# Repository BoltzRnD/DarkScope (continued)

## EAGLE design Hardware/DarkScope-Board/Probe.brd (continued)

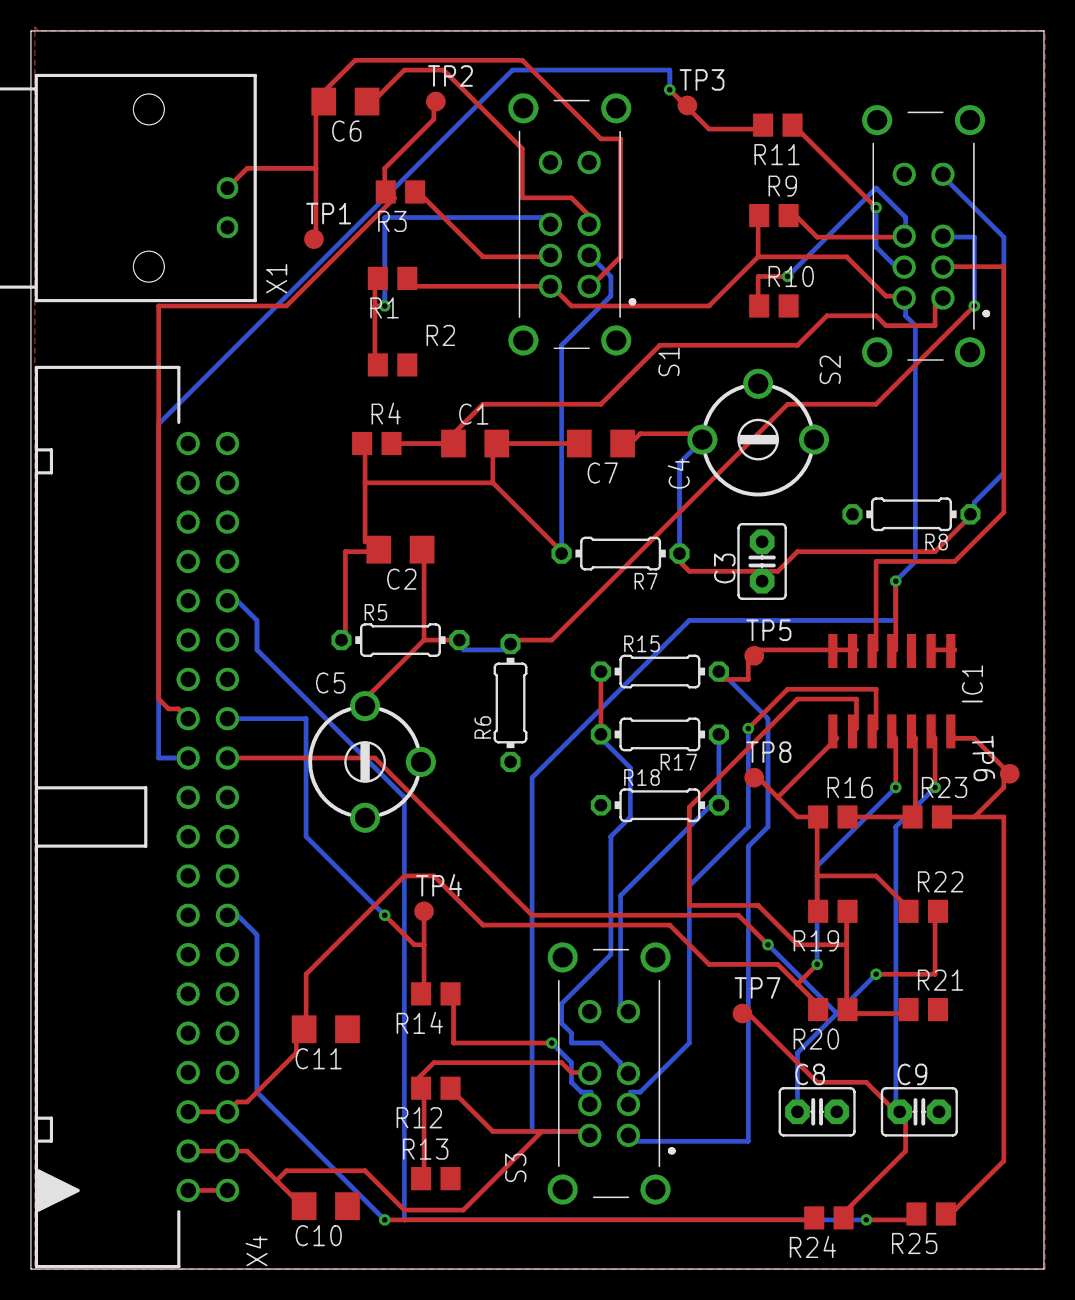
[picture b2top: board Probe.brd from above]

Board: 2 copper layers, 65.5 x 80.0 mm, 50 parts (0 on the bottom side), 33 nets.

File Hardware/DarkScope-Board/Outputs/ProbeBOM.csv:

"Part";"Value";"Device";"Package";"Description";"ARROW_PART_NUMBER";"ARROW_PRICE-STOCK";"DESCRIPTION";"HEIGHT";"MANUFACTURER_NAME";"MANUFACTURER_PART_NUMBER";"MF";"MOUSER_PART_NUMBER";"MOUSER_PRICE-STOCK";"MPN";"OC_FARNELL";"OC_NEWARK";"POPULARITY";"SPICEPREFIX";"TP_SIGNAL_NAME";
"C1";"220pF";"C-EUC1206";"C1206";"CAPACITOR, European symbol";"";"";"";"";"";"";"";"";"";"";"";"";"54";"C";"";
"C2";"3pF";"C-EUC1206";"C1206";"CAPACITOR, European symbol";"";"";"";"";"";"";"";"";"";"";"";"";"54";"C";"";
"C3";"120pF";"C2,5-3";"C2.5-3";"CAPACITOR";"";"";"";"";"";"";"";"";"";"";"";"";"38";"";"";
"C4";"30pF";"C-TRIMM808";"CTRIM808-BC";"Trimm capacitor";"";"";"";"";"";"";"";"";"";"";"";"";"3";"C";"";
"C5";"30pF";"C-TRIMM808";"CTRIM808-BC";"Trimm capacitor";"";"";"";"";"";"";"";"";"";"";"";"";"3";"C";"";
"C6";"0.1u";"C-EUC1206";"C1206";"CAPACITOR, European symbol";"";"";"";"";"";"";"";"";"";"";"";"";"54";"C";"";
"C7";"1pF";"C-EUC1206";"C1206";"CAPACITOR, European symbol";"";"";"";"";"";"";"";"";"";"";"";"";"54";"C";"";
"C8";"120pF";"C2,5-3";"C2.5-3";"CAPACITOR";"";"";"";"";"";"";"";"";"";"";"";"";"38";"";"";
"C9";"0.1u";"C2,5-3";"C2.5-3";"CAPACITOR";"";"";"";"";"";"";"";"";"";"";"";"";"38";"";"";
"C10";"0.1uF";"C-EUC1206";"C1206";"CAPACITOR, European symbol";"";"";"";"";"";"";"";"";"";"";"";"";"54";"C";"";
"C11";"0.1uF";"C-EUC1206";"C1206";"CAPACITOR, European symbol";"";"";"";"";"";"";"";"";"";"";"";"";"54";"C";"";
"IC1";"TL084D";"TL084D";"SO14";"OP AMP";"";"";"";"";"";"";"";"";"";"";"";"";"4";"X";"";
"R1";"10K";"R-US_R0805";"R0805";"RESISTOR, American symbol";"";"";"";"";"";"";"";"";"";"";"";"";"85";"R";"";
"R2";"3.3K";"R-US_R0805";"R0805";"RESISTOR, American symbol";"";"";"";"";"";"";"";"";"";"";"";"";"85";"R";"";
"R3";"1.5K";"R-US_R0805";"R0805";"RESISTOR, American symbol";"";"";"";"";"";"";"";"";"";"";"";"";"85";"R";"";
"R4";"100K";"R-US_R0805";"R0805";"RESISTOR, American symbol";"";"";"";"";"";"";"";"";"";"";"";"";"85";"R";"";
"R5";"1.8M 1%";"R-EU_0204/7";"0204/7";"RESISTOR, European symbol";"";"";"";"";"";"";"";"";"";"";"";"";"79";"R";"";
"R6";"200K 1%";"R-EU_0204/7";"0204/7";"RESISTOR, European symbol";"";"";"";"";"";"";"";"";"";"";"";"";"79";"R";"";
"R7";"2M 1%";"R-EU_0204/7";"0204/7";"RESISTOR, European symbol";"";"";"";"";"";"";"";"";"";"";"";"";"79";"R";"";
"R8";"20K 1%";"R-EU_0204/7";"0204/7";"RESISTOR, European symbol";"";"";"";"";"";"";"";"";"";"";"";"";"79";"R";"";
"R9";"10K";"R-US_R0805";"R0805";"RESISTOR, American symbol";"";"";"";"";"";"";"";"";"";"";"";"";"85";"R";"";
"R10";"3.3K";"R-US_R0805";"R0805";"RESISTOR, American symbol";"";"";"";"";"";"";"";"";"";"";"";"";"85";"R";"";
"R11";"1.5K";"R-US_R0805";"R0805";"RESISTOR, American symbol";"";"";"";"";"";"";"";"";"";"";"";"";"85";"R";"";
"R12";"10K";"R-US_R0805";"R0805";"RESISTOR, American symbol";"";"";"";"";"";"";"";"";"";"";"";"";"85";"R";"";
"R13";"3.3K";"R-US_R0805";"R0805";"RESISTOR, American symbol";"";"";"";"";"";"";"";"";"";"";"";"";"85";"R";"";
"R14";"1.5K";"R-US_R0805";"R0805";"RESISTOR, American symbol";"";"";"";"";"";"";"";"";"";"";"";"";"85";"R";"";
"R15";"300E";"R-EU_0204/7";"0204/7";"RESISTOR, European symbol";"";"";"";"";"";"";"";"";"";"";"";"";"79";"R";"";
"R16";"120e";"R-US_R0805";"R0805";"RESISTOR, American symbol";"";"";"";"";"";"";"";"";"";"";"";"";"85";"R";"";
"R17";"180E";"R-EU_0204/7";"0204/7";"RESISTOR, European symbol";"";"";"";"";"";"";"";"";"";"";"";"";"79";"R";"";
"R18";"120E";"R-EU_0204/7";"0204/7";"RESISTOR, European symbol";"";"";"";"";"";"";"";"";"";"";"";"";"79";"R";"";
"R19";"1K";"R-US_R0805";"R0805";"RESISTOR, American symbol";"";"";"";"";"";"";"";"";"";"";"";"";"85";"R";"";
"R20";"3K";"R-US_R0805";"R0805";"RESISTOR, American symbol";"";"";"";"";"";"";"";"";"";"";"";"";"85";"R";"";
"R21";"150E";"R-US_R0805";"R0805";"RESISTOR, American symbol";"";"";"";"";"";"";"";"";"";"";"";"";"85";"R";"";
"R22";"120E";"R-US_R0805";"R0805";"RESISTOR, American symbol";"";"";"";"";"";"";"";"";"";"";"";"";"85";"R";"";
"R23";"100k";"R-US_R0805";"R0805";"RESISTOR, American symbol";"";"";"";"";"";"";"";"";"";"";"";"";"85";"R";"";
"R24";"100K";"R-US_R0805";"R0805";"RESISTOR, American symbol";"";"";"";"";"";"";"";"";"";"";"";"";"85";"R";"";
"R25";"1k";"R-US_R0805";"R0805";"RESISTOR, American symbol";"";"";"";"";"";"";"";"";"";"";"";"";"85";"R";"";
"S1";"DC-AC-GND";"EG2301";"EG2301";"Slide Switches DP3T PC MNT SLIDE";"";"";"Slide Switches DP3T PC MNT SLIDE";"11mm";"E-Switch";"EG2301";"";"612-EG2301";"https://www.mouser.co.uk/ProductDetail/E-Switch/EG2301?qs=6C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";"";"";"";"";"";"";
"S2";"EG2301";"EG2301";"EG2301";"Slide Switches DP3T PC MNT SLIDE";"";"";"Slide Switches DP3T PC MNT SLIDE";"11mm";"E-Switch";"EG2301";"";"612-EG2301";"https://www.mouser.co.uk/ProductDetail/E-Switch/EG2301?qs=6C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";"";"";"";"";"";"";
"S3";"EG2301";"EG2301";"EG2301";"Slide Switches DP3T PC MNT SLIDE";"";"";"Slide Switches DP3T PC MNT SLIDE";"11mm";"E-Switch";"EG2301";"";"612-EG2301";"https://www.mouser.co.uk/ProductDetail/E-Switch/EG2301?qs=6C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";"";"";"";"";"";"";
"TP1";"TPB1,27";"TPB1,27";"B1,27";"Test pad";"";"";"";"";"";"";"";"";"";"";"";"";"19";"";"";
"TP2";"TPB1,27";"TPB1,27";"B1,27";"Test pad";"";"";"";"";"";"";"";"";"";"";"";"";"19";"";"";
"TP3";"TPB1,27";"TPB1,27";"B1,27";"Test pad";"";"";"";"";"";"";"";"";"";"";"";"";"19";"";"";
"TP4";"TPB1,27";"TPB1,27";"B1,27";"Test pad";"";"";"";"";"";"";"";"";"";"";"";"";"19";"";"";
"TP5";"TPB1,27";"TPB1,27";"B1,27";"Test pad";"";"";"";"";"";"";"";"";"";"";"";"";"19";"";"";
"TP6";"TPB1,27";"TPB1,27";"B1,27";"Test pad";"";"";"";"";"";"";"";"";"";"";"";"";"19";"";"";
"TP7";"TPB1,27";"TPB1,27";"B1,27";"Test pad";"";"";"";"";"";"";"";"";"";"";"";"";"19";"";"";
"TP8";"TPB1,27";"TPB1,27";"B1,27";"Test pad";"";"";"";"";"";"";"";"";"";"";"";"";"19";"";"";
"X1";"1-227161-0";"1-227161-0";"AMP_227161";"JACK,  RIGHT ANGLE, 50 OHM, PCB, BNC";"";"";"";"";"";"";"TYCO ELECTRONICS";"";"";"1-227161";"unknown";"33B3200";"0";"";"";
"X4";"2540-5";"2540-5";"PAK100/2500-5-40";"3M (TM) Pak 100 4-Wall Header";"";"";"";"";"";"";"";"";"";"";"9838414";"unknown";"0";"";"";

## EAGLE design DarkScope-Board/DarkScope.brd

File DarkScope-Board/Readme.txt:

This Folder will be Updated with Schematics and Board Files For the Darkscope.

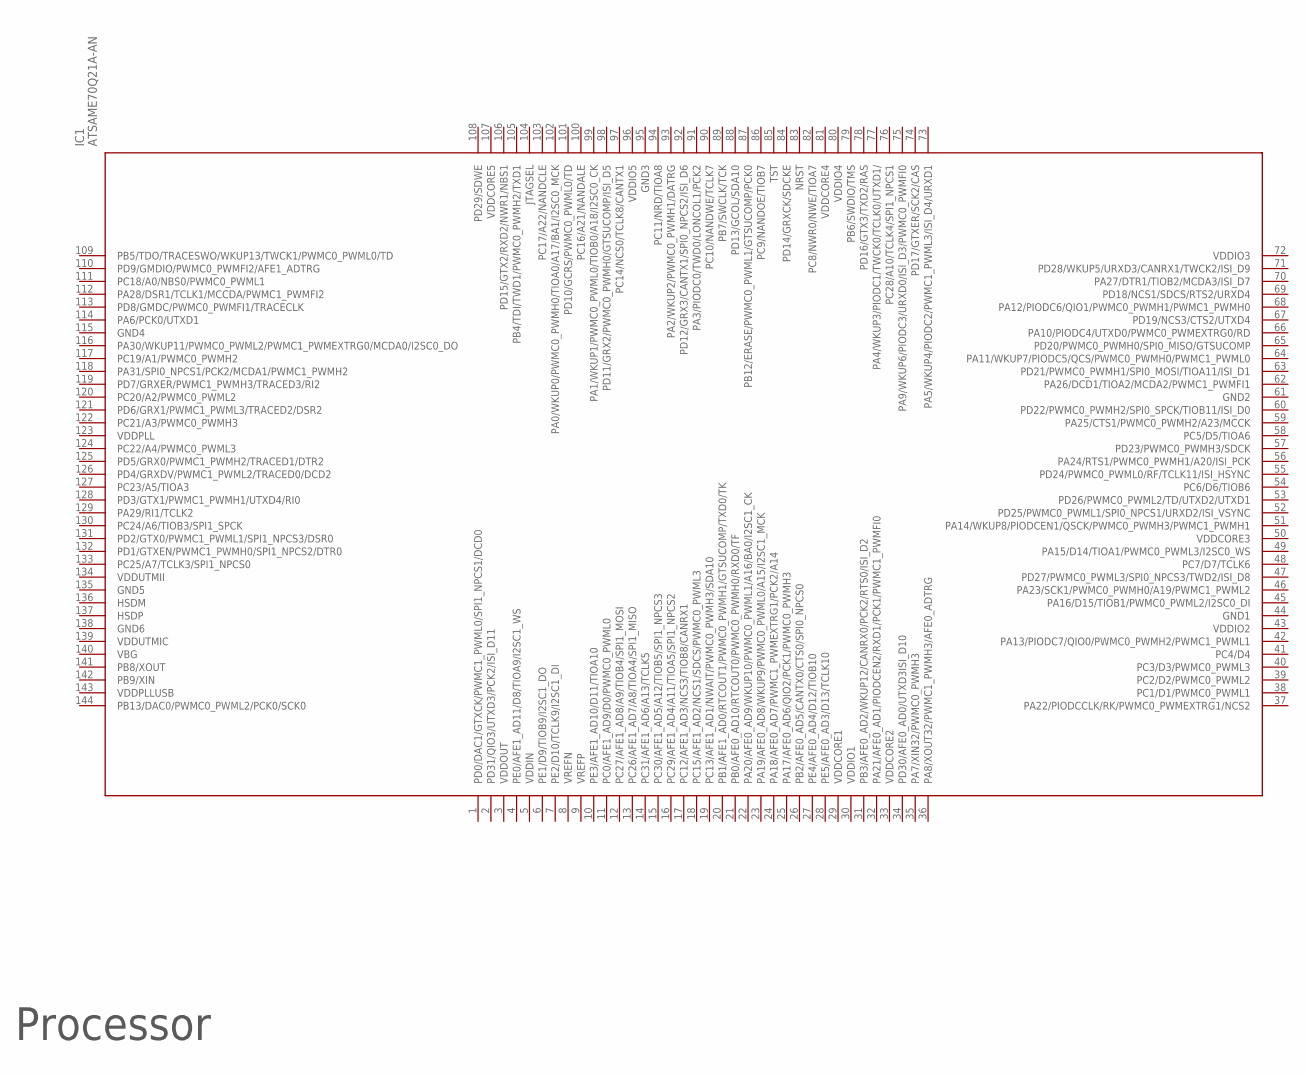
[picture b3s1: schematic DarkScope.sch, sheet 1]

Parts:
IC1: ATSAME70Q21A-AN; QFP50P2200X2200X160-144N

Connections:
GND1: IC1.44 (GND1)
GND2: IC1.61 (GND2)
GND3: IC1.95 (GND3)
GND4: IC1.115 (GND4)
GND5: IC1.135 (GND5)
GND6: IC1.138 (GND6)
VDDCORE1: IC1.29 (VDDCORE1)
VDDCORE2: IC1.33 (VDDCORE2)
VDDCORE3: IC1.50 (VDDCORE3)
VDDCORE4: IC1.81 (VDDCORE4)
VDDCORE5: IC1.107 (VDDCORE5)
VDDIN: IC1.5 (VDDIN)
VDDIO1: IC1.30 (VDDIO1)
VDDIO2: IC1.43 (VDDIO2)
VDDIO3: IC1.72 (VDDIO3)
VDDIO4: IC1.80 (VDDIO4)
VDDIO5: IC1.96 (VDDIO5)
VDDOUT: IC1.3 (VDDOUT)
VDDPLL: IC1.123 (VDDPLL)
VDDPLLUSB: IC1.143 (VDDPLLUSB)
VDDUTMIC: IC1.139 (VDDUTMIC)
VDDUTMII: IC1.134 (VDDUTMII)

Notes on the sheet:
Processor

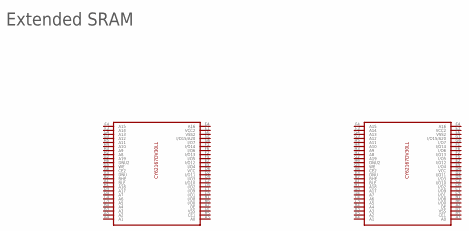
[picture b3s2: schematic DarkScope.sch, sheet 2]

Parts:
U$22, U$23: CY62167DV30LLCY62167DV30LL-55BVI; BGA48C75P6X8_950X800X100

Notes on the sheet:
Extended SRAM

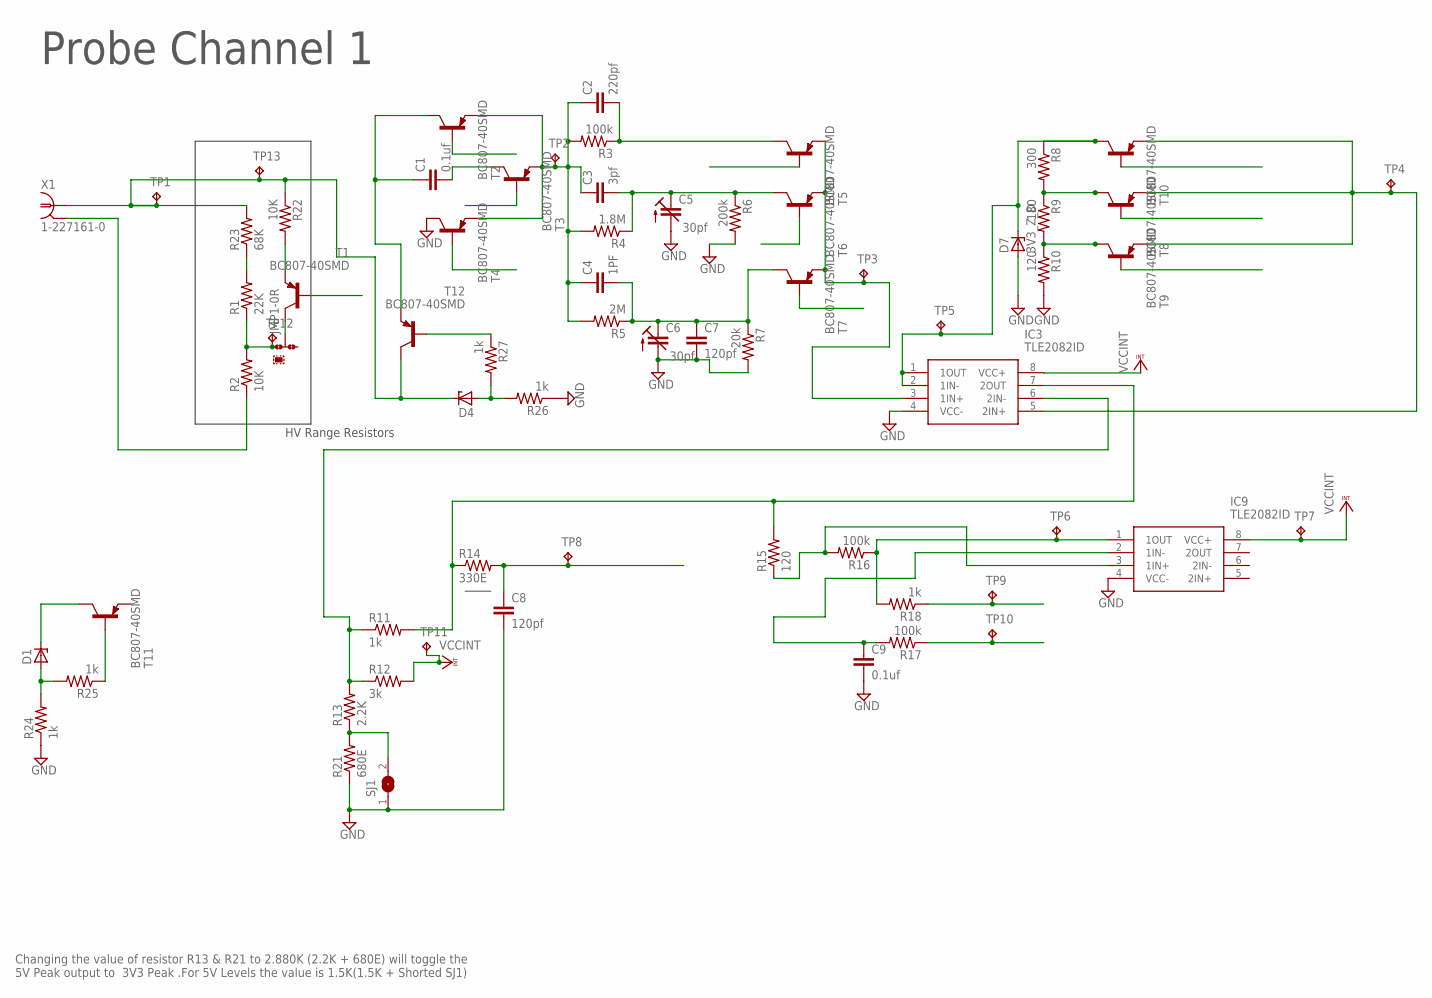
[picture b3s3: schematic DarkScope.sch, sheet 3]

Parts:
C1, C9: 0.1uf; C0603
C2: 220pf; C0603
C3: 3pf; C0603
C4: 1PF; C0603
C5, C6: 30pf; CTRIM3018_11
C7, C8: 120pf; C0603
D1, D4: ZENER-DIODESOD80C; SOD80C
D7: 3V3_Z_D; SOD80C
IC3, IC9: TLE2082ID; SOIC127P600X175-8N
JMP1: 0R-JUMPC; C0R-JMP
R1: 22K; R0603
R2, R22: 10K; R0603
R3, R16, R17: 100k; R0603
R4: 1.8M; R0603
R5: 2M; R0603
R6: 200k; R0603
R7: 20k; R0603
R8: 300; R0603
R9: 180; R0603
R10, R15: 120; R0603
R11, R18, R24, R25, R26, R27: 1k; R0603
R12: 3k; R0603
R13: 2.2K; R0603
R14: 330E; R0603
R21: 680E; R0603
R23: 68K; R0603
SJ1: SJ
T1, T2, T3, T4, T5, T6, T7, T8, T9, T10, T11, T12: BC807-40SMD; SOT23-BEC
TP1, TP2, TP3, TP4, TP5, TP6, TP7, TP8, TP9, TP10, TP11, TP12, TP13: TPTP07R; TP07R
X1: 1-227161-0; AMP_227161

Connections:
+5V/1: IC3.8 (VCC+), IC9.8 (VCC+), R12.2, TP7.TP, TP11.TP; also elsewhere on the board
GND: C5.- (A), C6.- (A), C7.2, C8.2, C9.2, D7.A, IC3.4 (VCC-), IC9.4 (VCC-), R6.2, R7.2, R10.2, R21.1, SJ1.1, T4.C; also elsewhere on the board
unnamed: R2.1, X1.2
unnamed: JMP1.1, R1.1, R2.2, TP12.TP
unnamed: C1.2, T3.C
unnamed: R8.2, R9.1, T8.C
unnamed: D4.C, R22.1, R23.2, T12.C, TP1.TP, TP13.TP, X1.1
unnamed: C2.1, C3.1, C4.1, R3.2, R4.2, R5.2, T2.E, T3.E, T4.E, TP2.TP
unnamed: C4.2, C6.+ (E), C7.1, R5.1, R7.1, T7.C
unnamed: C2.2, R3.1, T5.C
unnamed: C3.2, C5.+ (E), R4.1, R6.1, T6.C
unnamed: R9.2, R10.1, T9.C
unnamed: IC3.3 (1IN+), T5.E, T6.E, T7.E, TP3.TP
unnamed: IC3.5 (2IN+), T8.E, T9.E, T10.E, TP4.TP
unnamed: IC3.6 (2IN-), R11.1, R12.1, R13.2
unnamed: IC3.7 (2OUT), R11.2, R14.1, R15.2
unnamed: C8.1, R14.2, TP8.TP
unnamed: IC9.3 (1IN+), R15.1, R16.2
unnamed: IC9.1 (1OUT), R16.1, R18.2, TP6.TP
unnamed: C9.1, IC9.2 (1IN-), R17.2
unnamed: R17.1, TP10.TP
unnamed: R18.1, TP9.TP
unnamed: D7.C, IC3.1 (1OUT), IC3.2 (1IN-), R8.1, T10.C, TP5.TP
unnamed: R13.1, R21.2, SJ1.2
unnamed: R22.2, T1.E
unnamed: R1.2, R23.1
unnamed: JMP1.2, T1.C
unnamed: D1.A, R24.2, R25.2
unnamed: R25.1, T11.B
unnamed: D1.C, T11.C
unnamed: D4.A, R26.2, R27.2
unnamed: R27.1, T12.B
unnamed: C1.1, T2.C, T12.E

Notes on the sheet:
Probe Channel 1
HV Range Resistors
Changing the value of resistor R13 & R21 to 2.880K (2.2K + 680E) will toggle the 5V Peak output to 3V3 Peak .For 5V Levels the value is 1.5K(1.5K + Shorted SJ1)

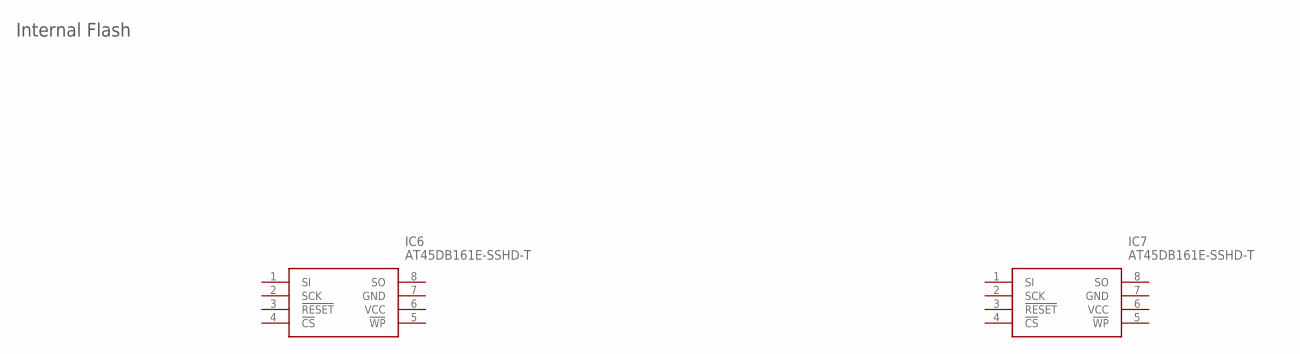
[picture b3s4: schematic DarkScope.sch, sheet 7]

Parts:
IC6, IC7: AT45DB161E-SSHD-T; SOIC127P600X175-8N

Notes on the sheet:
Internal Flash

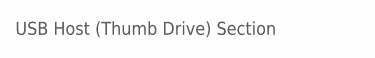
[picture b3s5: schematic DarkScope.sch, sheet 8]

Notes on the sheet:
USB Host (Thumb Drive) Section

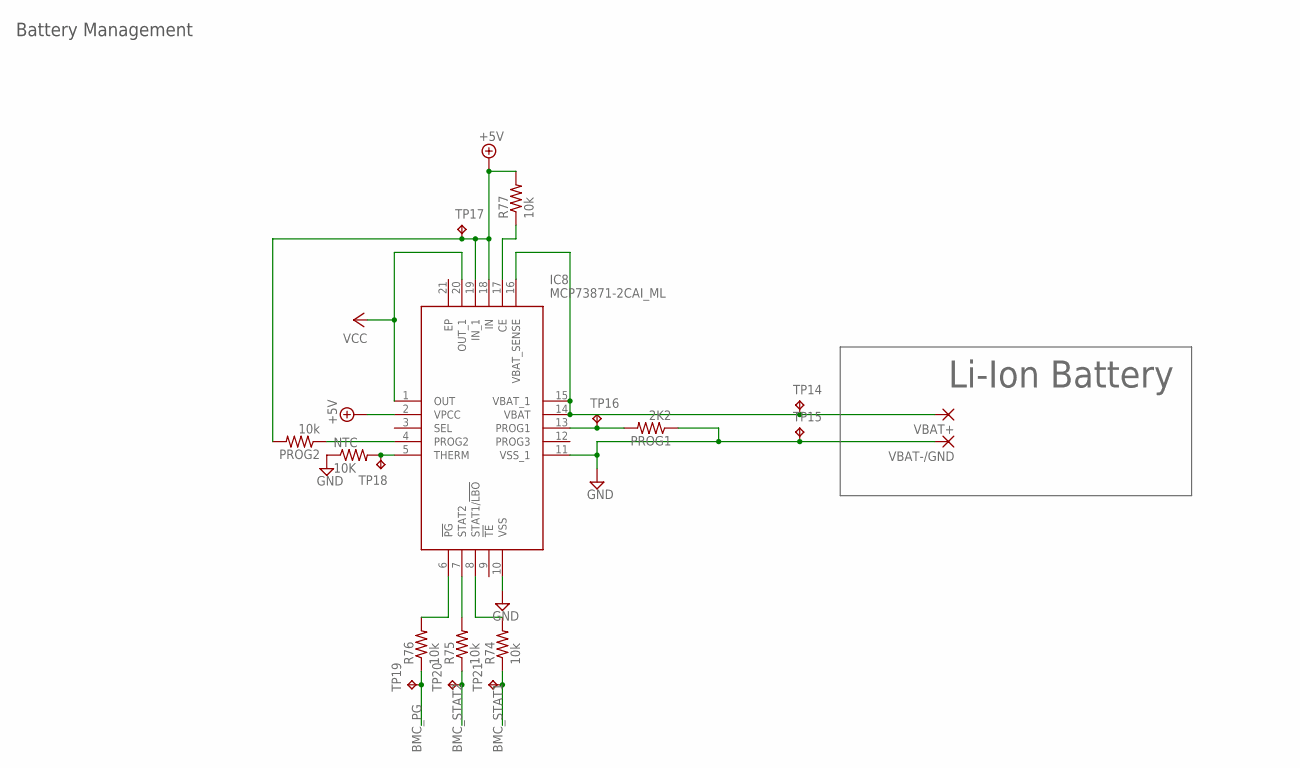
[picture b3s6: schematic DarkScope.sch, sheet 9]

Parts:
IC8: MCP73871-2CAI_ML; QFN50P400X400X100-21N
NTC: 10K; R0603
PROG1: 2K2; R0603
PROG2: 10k; R0603
R74, R75, R76, R77: 10k; R0603
TP14, TP15, TP16, TP17, TP18, TP19, TP20, TP21: TPTP07R; TP07R
VBAT+: SMD5; SMD2,54-5,08
VBAT-/GND: SMD5; SMD2,54-5,08

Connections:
+5V: IC8.2 (VPCC), IC8.18 (IN), IC8.19 (IN_1), PROG2.2, R77.2, TP17.TP; also elsewhere on the board
BMC_PG: R76.1, TP19.TP
BMC_STAT1: R74.1, TP21.TP
BMC_STAT2: R75.1, TP20.TP
GND: IC8.10 (VSS), IC8.11 (VSS_1), PROG1.1, TP15.TP, VBAT-/GND.1; also elsewhere on the board
unnamed: IC8.8 (STAT1/!LBO), R74.2
unnamed: IC8.5 (THERM), NTC.2, TP18.TP
unnamed: IC8.6 (!PG), R76.2
unnamed: IC8.7 (STAT2), R75.2
unnamed: IC8.13 (PROG1), PROG1.2, TP16.TP
unnamed: IC8.14 (VBAT), IC8.15 (VBAT_1), IC8.16 (VBAT_SENSE), TP14.TP, VBAT+.1
unnamed: IC8.4 (PROG2), PROG2.1
unnamed: IC8.17 (CE), R77.1
VCC: IC8.1 (OUT), IC8.20 (OUT_1); also elsewhere on the board

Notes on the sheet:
Battery Management
Li-Ion Battery

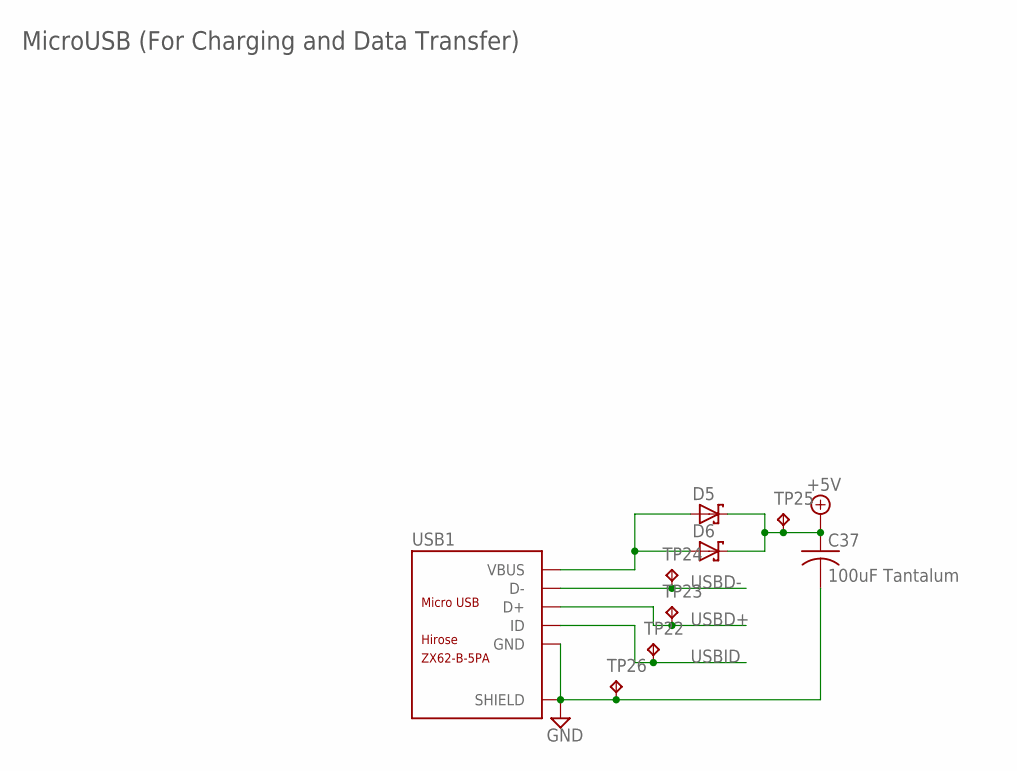
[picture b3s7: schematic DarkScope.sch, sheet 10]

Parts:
C37: 100uF Tantalum; C1206
D5, D6: SCHOTTKY-DIODESMC; DIODE_SMC
TP22, TP23, TP24, TP25, TP26: TPTP07R; TP07R
USB1: ZX62-B-5PA; MICRO-USB5+6P-SMD-0.65-AB

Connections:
+5V: C37.1, D5.C (A), D6.C (A), TP25.TP; also elsewhere on the board
GND: C37.2, TP26.TP, USB1.5 (GND), USB1.P1 (SHIELD), USB1.P2 (SHIELD), USB1.P3 (SHIELD), USB1.P4 (SHIELD), USB1.P5 (SHIELD), USB1.P6 (SHIELD); also elsewhere on the board
USBD+: TP23.TP, USB1.3 (D+)
USBD-: TP24.TP, USB1.2 (D-)
USBID: TP22.TP, USB1.4 (ID)
VBUS: D5.A (C), D6.A (C), USB1.1 (VBUS)

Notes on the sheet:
MicroUSB (For Charging and Data Transfer)

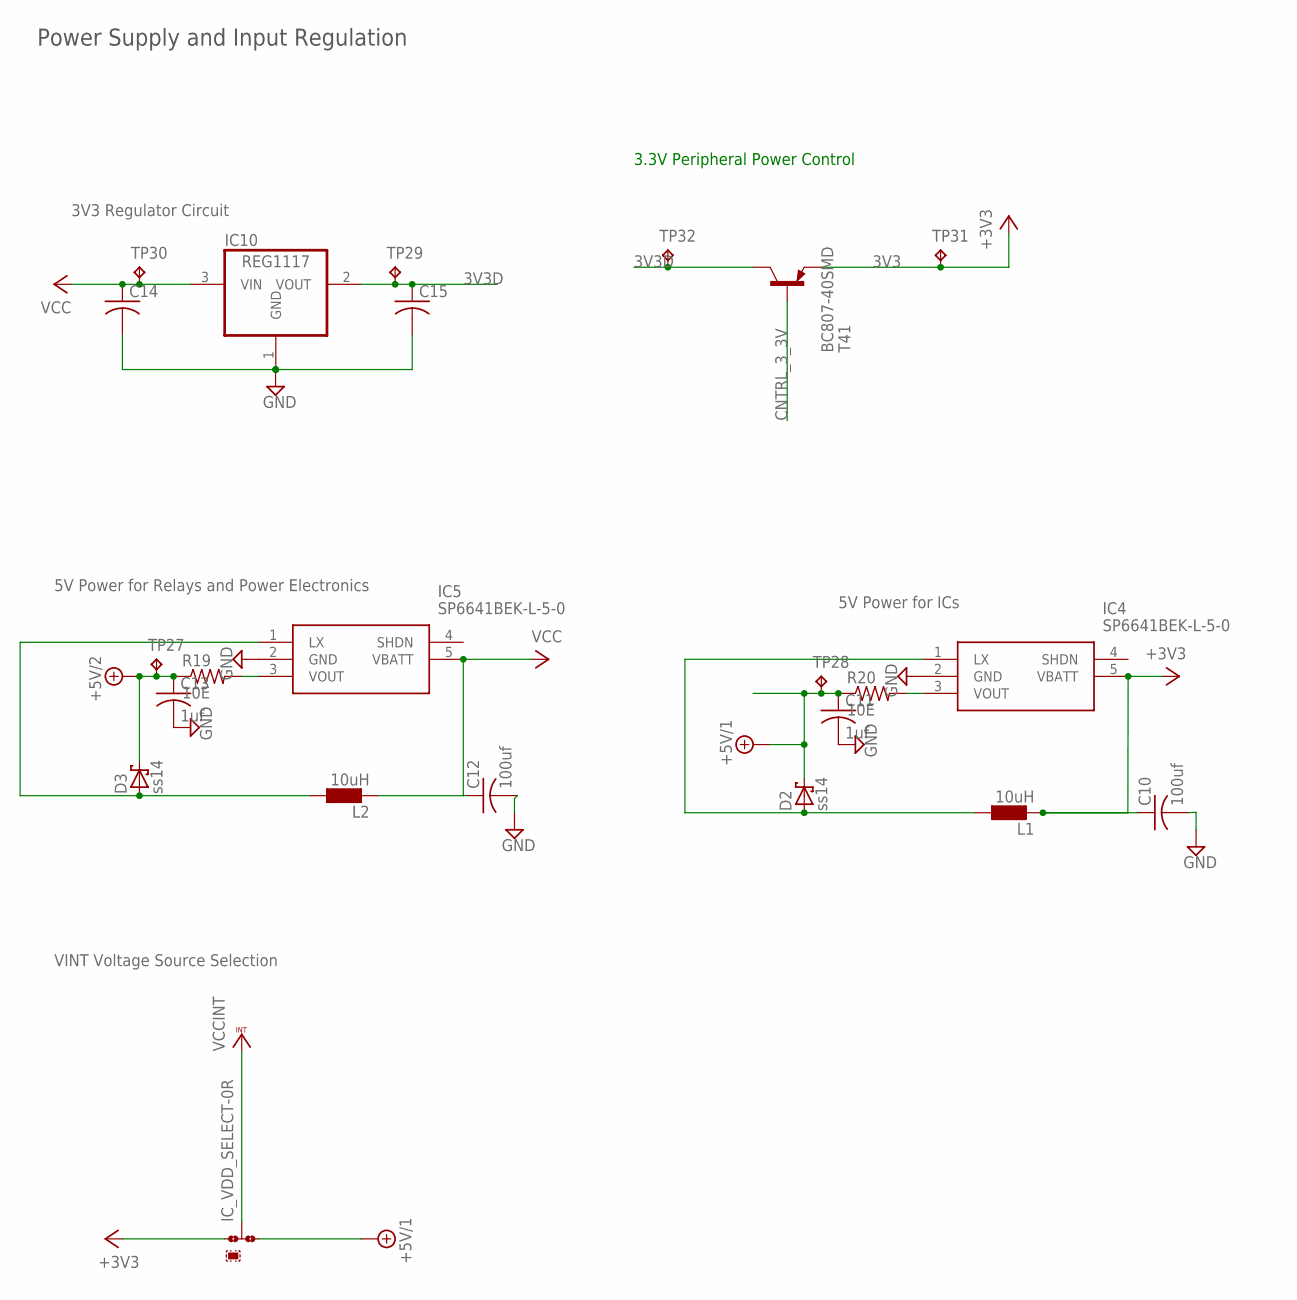
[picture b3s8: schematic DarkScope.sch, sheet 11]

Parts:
C10, C12: 100uf; C0603K
C11, C13: 1uf; C0603K
C14, C15: C-USC0603K; C0603K
D2, D3: ss14; SMC
IC4, IC5: SP6641BEK-L-5-0; SOT95P280X145-5N
IC10: REG1117; SOT223
IC_VDD_SELECT: 0R-JUMPC; C0R-JMP
L1, L2: 10uH; 0204/7
R19, R20: 10E; R0603
T41: BC807-40SMD; SOT23-BEC
TP27, TP28, TP29, TP30, TP31, TP32: TPTP07R; TP07R

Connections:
3V3: T41.E, TP31.TP
3V3D: C15.1, IC10.2 (VOUT), T41.C, TP29.TP, TP32.TP
+3V3: C10.1, IC4.5 (VBATT), IC_VDD_SELECT.1, L1.2
+5V/1: C11.1, D2.C, IC_VDD_SELECT.3, R20.1, TP28.TP; also elsewhere on the board
+5V/2: C13.1, D3.C, R19.1, TP27.TP
CNTRL_3_3V: T41.B
GND: C10.2, C11.2, C12.2, C13.2, C14.2, C15.2, IC4.2 (GND), IC5.2 (GND), IC10.1 (GND); also elsewhere on the board
unnamed: D2.A, IC4.1 (LX), L1.1
unnamed: IC4.3 (VOUT), R20.2
unnamed: IC5.3 (VOUT), R19.2
unnamed: D3.A, IC5.1 (LX), L2.1
VCC: C12.1, C14.1, IC5.5 (VBATT), IC10.3 (VIN), L2.2, TP30.TP; also elsewhere on the board
VCCINT: IC_VDD_SELECT.2

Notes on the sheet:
Power Supply and Input Regulation
3.3V Peripheral Power Control
5V Power for ICs
5V Power for Relays and Power Electronics
3V3 Regulator Circuit
VINT Voltage Source Selection

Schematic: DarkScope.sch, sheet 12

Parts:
SD1: ST-TF-003A; MICRO-SD9+4P-SMD-16.1X14.5X1.85MM

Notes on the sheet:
MicroSD Section

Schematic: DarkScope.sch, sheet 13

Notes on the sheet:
Switching Circuitry

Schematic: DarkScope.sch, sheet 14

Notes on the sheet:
RCA Out

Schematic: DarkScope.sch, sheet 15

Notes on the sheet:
VGA Out

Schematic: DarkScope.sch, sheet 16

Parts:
U$20, U$21: MAX19516ETM+MAX19516ETM+; QFN50P700X700X80-48

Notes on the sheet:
HIGH SPEED ADC
Channel 1
Channel 2

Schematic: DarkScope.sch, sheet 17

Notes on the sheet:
4.5"/7" LCD

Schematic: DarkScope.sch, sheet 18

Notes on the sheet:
Sample Wave

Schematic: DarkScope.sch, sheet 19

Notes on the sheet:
Switches

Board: 2 copper layers, 125 parts (0 on the bottom side), 58 nets, no tracks yet.

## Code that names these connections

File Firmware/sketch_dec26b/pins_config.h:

#define SERIAL_BAUD_RATE	250000

// analog and digital samples storage depth
#define NUM_SAMPLES 	2048	

// pin definitions (DSO138)
#define BOARD_LED 		PA15
#define TEST_WAVE_PIN 	PA7     // 1KHz square wave output
#define TRIGGER_IN		PA8
#define TRIGGER_LEVEL	PB8
#define VGEN			PB9		// used to generate negative voltage in DSO138

// captured inputs
#define AN_CH1 			PA0		// analog channel 1
#define AN_CH2 			PA4		// analog channel 2
#define DG_CH1 			PA13	// digital channel 1 - 5V tolerant pin. Pin mask throughout code has to match digital pin
#define DG_CH2 			PA14	// digital channel 2 - 5V tolerant pin. Pin mask throughout code has to match digital pin

// misc analog inputs
#define VSENSSEL1 		PA2
#define VSENSSEL2		PA1
#define CPLSEL			PA3

#define LED_ON	digitalWrite(BOARD_LED, LOW)
#define LED_OFF	digitalWrite(BOARD_LED, HIGH)

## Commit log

2018-05-05 Backlink to CADLAB.io has been added.
2018-05-05 Created Readme For PC Host
2018-05-05 Created ReadMe File For ScopeSoul
2018-05-05 Created ReadMe For Circuit's Folder
2018-05-05 Fixed a Typo In readme
2018-05-05 Fixed a Typo
2018-05-05 Added Under Development Schematic
2018-05-05 Added BNC Connectors
2018-05-23 Added Circuits
    Added circuitry for 4 channels and Op amps
2018-05-23 Cleaned Garbage Files
2018-06-14 Selected and Added More Devices
    Added ADC,Battery Management IC,Flash and more.
2018-06-14 Added Devices and Connections
    Added Devices and Connections
2018-06-15 Added Components and Modified Conections
    Updated The OP-amps and BJTs and modified connections.
2018-12-21 Updated Files and Timeline
    Updated the timeline for product completetion, and backed up last saved work.
2021-09-29 Added Submodule for Source FW
2021-09-29 CP Added MCU and Supporting Periph
2021-09-30 CP PSU
2021-09-30 CP PSU Completed
2021-10-01 Added LCD Header
2021-10-17 BaseBoard Schematic Complete
2021-10-23 BB DP
2021-10-23 CP Component Placements
2021-10-23 Cp BB Placement Completed
2021-10-23 UnRouted Board Bkp
2021-10-23 CP BB PCB Draft
2021-10-23 Added Mounting Holes
2021-10-23 Added PCB Holes for Mounting
2021-10-24 Sim Model DP
2021-10-24 Dp Clipping Positive Cycle
2021-10-24 DP Wtf
2021-11-16 DP Probe SCH
2021-11-17 Drafted Sch for Probe Board
2021-11-18 Fixed baseboard
2021-11-19 Unrouted Probe Board
2021-11-19 Routed Probe Board
2021-11-19 Cleared and Fixed Probe Board's ERC Errors
2021-12-10 Updated Board Dimension and Added Gerbers
2021-12-10 Fixed BaseBoard Bugs
    1. Ground Plane Not connected Properly
    2. C14,C15 Reversed.
2021-12-10 Added Final Probe CAM Outputs
2021-12-10 Added BOMs
2021-12-12 Updated BaseBoard as per DFM Request
2021-12-26 Bare Minimum FW and SW Files Init
2021-12-28 DP FW
2021-12-28 Added UI Frontend
